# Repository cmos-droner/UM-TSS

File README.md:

# UM-TSS - CMOS Drumsynth
This is a circuit by Jacob Watters ([check the original block post](http://www.jacobwatters.com/blog/um-tss-drum-machine/)), I just did the PCB-layout. In agreement with Jacob this is released here as open hardware. Hopefully you enjoy the project and maybe you can even improve it!

## The circuit
The circuit is based around a couple of 40106 hex-schmitt triggers. I removed the divider from Jacobs layout to make every sound triggerable by itself. The trigger ins are protected by clamping diodes.

## PCB v1
PCB v1 has a couple of bugs (mainly because I used the wrong revision of Jacobs circuit **duh**). But the PCB can certainly be used to build a running circuit. Check the build guide for PCB rev. 1 [here](https://github.com/tommueller/UM-TSS/blob/master/schematics%20v1/BUILD.md) and the [BOM](https://github.com/tommueller/UM-TSS/blob/master/schematics%20v1/BOM.ods?raw=true)

## PCB v2
I already fixed most of the issued in the schematics for version 2. I hope that together we can make a second version of the PCB that runs more smooth!

## Case
I created a case which can be fabbed by a lasercutter. The SVG is available in the repo. The plans are for 3mm material! Here is an image of the first finished prototype (3mm colored HDF):

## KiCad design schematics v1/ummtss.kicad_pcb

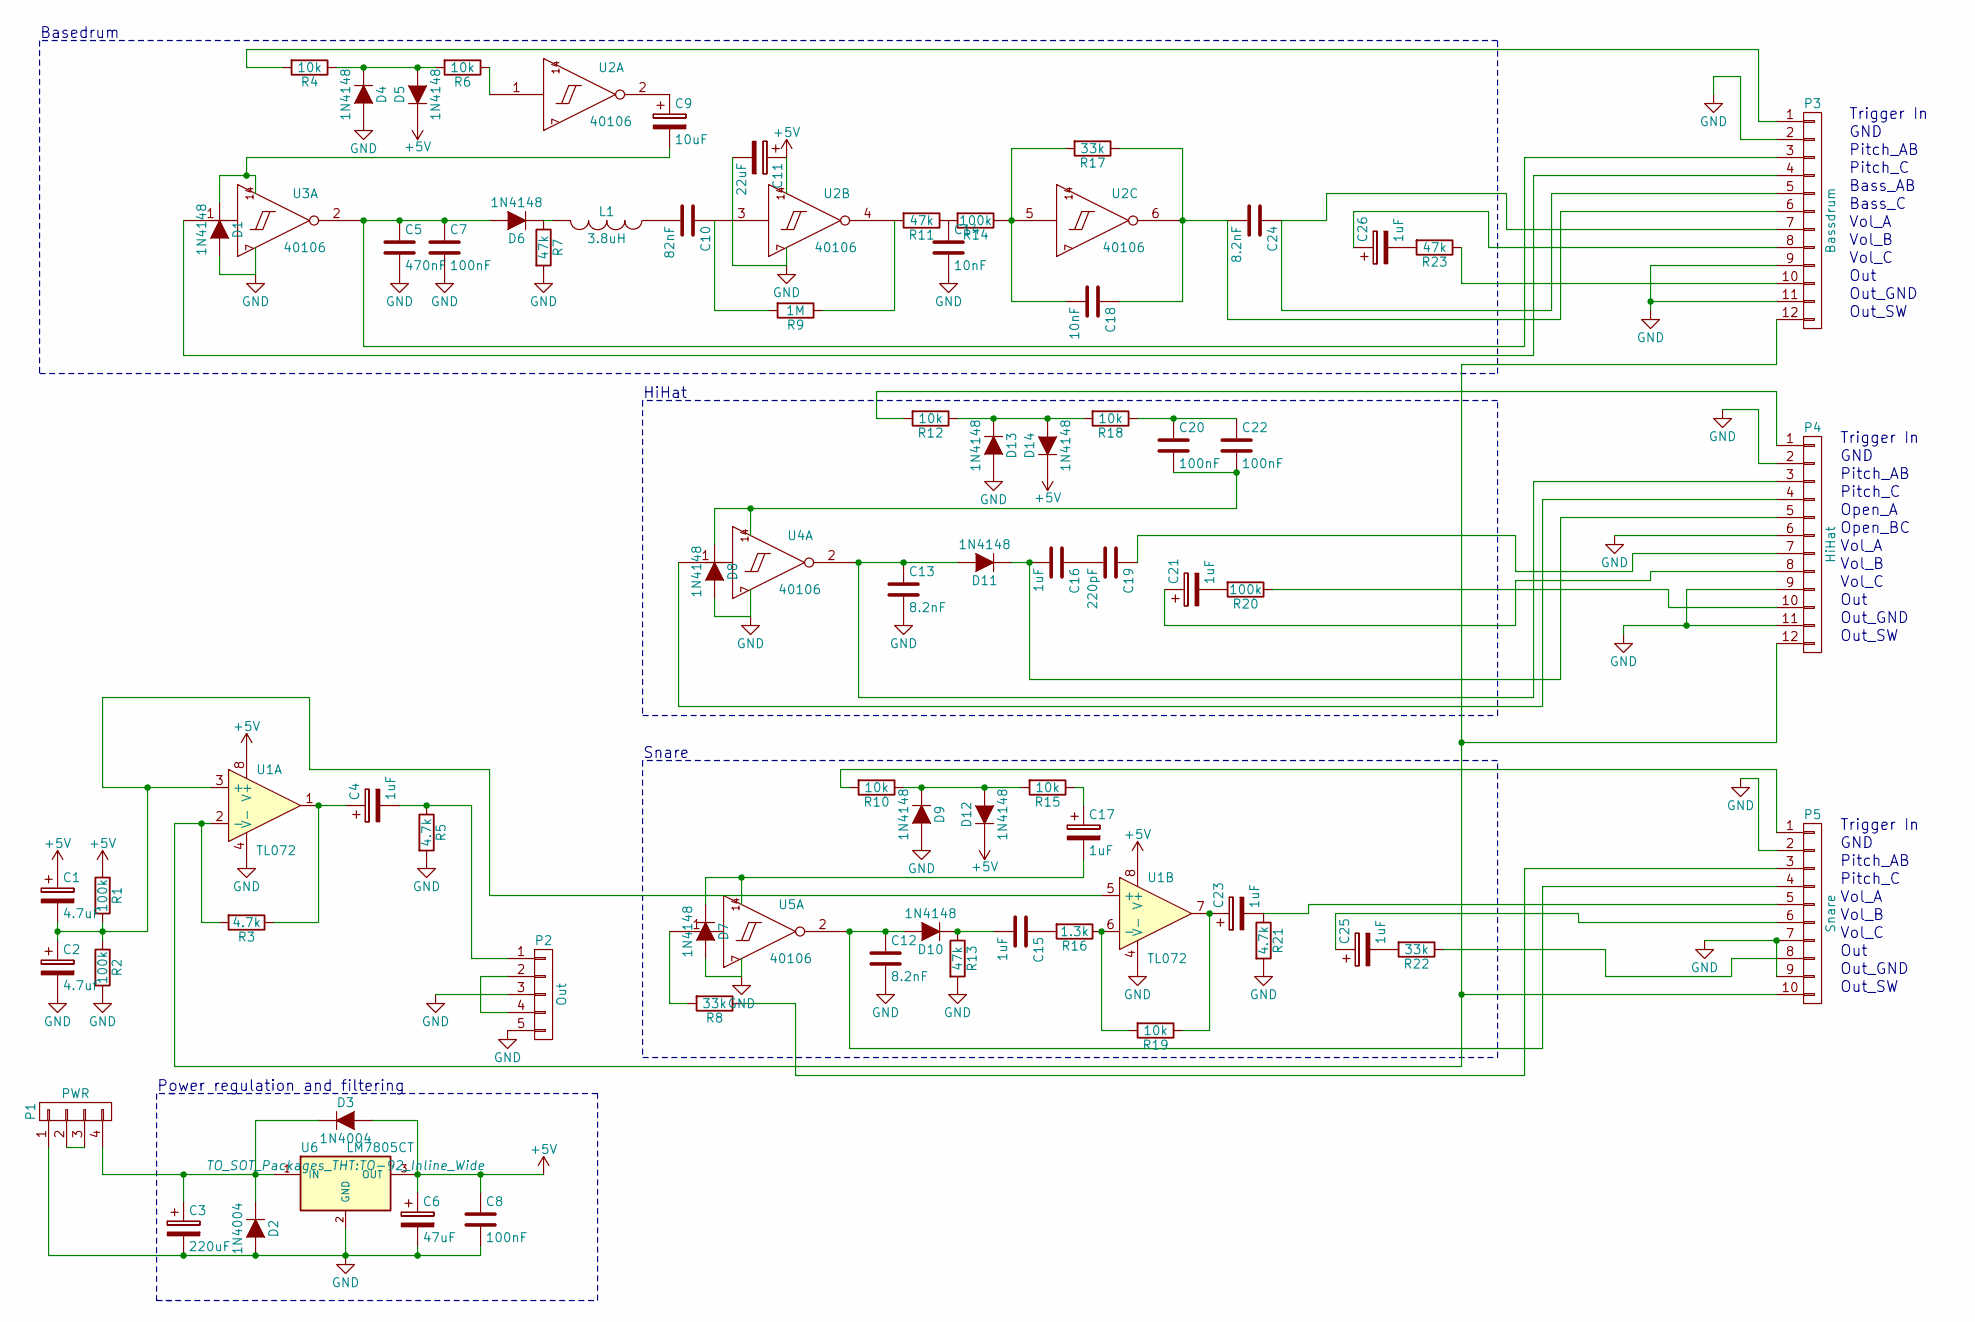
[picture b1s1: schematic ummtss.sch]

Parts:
C1: 4.7uF; C_Radial_D5_L11_P2.5
C2: 4.7uf; C_Radial_D5_L11_P2.5
C3: 220uF; C_Radial_D8_L11.5_P3.5
C4, C15, C16, C17, C21, C23, C25, C26: 1uF; C_Radial_D5_L11_P2.5
C5: 470nF; C_Rect_L4.5_W2.5_P3
C6: 47uF; C_Radial_D6.3_L11.2_P2.5
C7, C8, C20, C22: 100nF; C_Rect_L4.5_W2.5_P3
C9: 10uF; C_Radial_D5_L11_P2.5
C10: 82nF; C_Rect_L4.5_W2.5_P3
C11: 22uF; C_Radial_D5_L11_P2
C12, C13, C24: 8.2nF; C_Rect_L4.5_W2.5_P3
C14, C18: 10nF; C_Rect_L4.5_W2.5_P3
C19: 220pF; C_Rect_L4.5_W2.5_P3
D1, D4, D5, D6, D7, D8, D9, D10, D11, D12, D13, D14: 1N4148; Diode_DO-35_SOD27_Horizontal_RM10
D2, D3: 1N4004; Diode_DO-41_SOD81_Horizontal_RM10
L1: 3.8uH; Resistor_Horizontal_RM7mm_Wide
P1: PWR; Pin_Header_Straight_1x04
P2: Out; Pin_Header_Straight_1x05
P3: Bassdrum; Pin_Header_Straight_1x12
P4: HiHat; Pin_Header_Straight_1x12
P5: Snare; Pin_Header_Straight_1x10
R1, R2, R14, R20: 100k; Resistor_Horizontal_RM7mm_Wide
R3, R5, R21: 4.7k; Resistor_Horizontal_RM7mm_Wide
R4, R6, R10, R12, R15, R18, R19: 10k; Resistor_Horizontal_RM7mm_Wide
R7, R11, R13, R23: 47k; Resistor_Horizontal_RM7mm_Wide
R8, R17, R22: 33k; Resistor_Horizontal_RM7mm_Wide
R9: 1M; Resistor_Horizontal_RM7mm_Wide
R16: 1.3k; Resistor_Horizontal_RM7mm_Wide
U1: TL072; DIP-8_W7.62mm_LongPads
U2, U3, U4, U5: 40106; DIP-14_W7.62mm_LongPads
U6: LM7805CT; TO-92_Inline_Wide

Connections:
+5V: C1.1, C6.1, C8.1, C11.1, D3.2 (A), D5.1 (K), D12.1 (K), D14.1 (K), R1.1, U1.8 (V+), U2.14 (VDD_IN), U6.3 (OUT)
GND: C2.2, C3.2, C5.2, C6.2, C7.2, C8.2, C11.2, C12.2, C13.2, C14.2, D1.2 (A), D2.2 (A), D4.2 (A), D7.2 (A), D8.2 (A), D9.2 (A), D13.2 (A), P1.1, P2.3, P2.5, P3.2, P3.9, P3.11, P4.2, P4.6, P4.9, P4.11, P5.2, P5.7, P5.9, R2.2, R5.2, R7.2, R13.2, R21.2, U1.4 (V-), U2.7 (VSS_IN), U3.7 (VSS_IN), U4.7 (VSS_IN), U5.7 (VSS_IN), U6.2 (GND); also elsewhere on the board
unnamed: C1.2, C2.1, R1.2, R2.1, U1.3 (+), U1.5 (+)
unnamed 3: C3.1, D2.1 (K), D3.1 (K), P1.4, U6.1 (IN); also elsewhere on the board
unnamed: C4.1, R3.1, U1.1
unnamed 5: C4.2, P2.1, R5.1; also elsewhere on the board
unnamed 6: C5.1, C7.1, D6.2 (A), P3.3, U3.2 (Out); also elsewhere on the board
unnamed: C9.1, U2.2 (Out)
unnamed: C9.2, D1.1 (K), U3.14 (VDD_IN)
unnamed: C10.1, R9.2, U2.3 (In)
unnamed: C10.2, L1.1
unnamed 11: C12.1, D10.2 (A), P5.4, U5.2 (Out); also elsewhere on the board
unnamed 12: C13.1, D11.2 (A), P4.3, U4.2 (Out); also elsewhere on the board
unnamed: C14.1, R11.1, R14.2
unnamed: C15.1, R16.2
unnamed: C15.2, D10.1 (K), R13.1
unnamed: C16.1, C19.2
unnamed 17: C16.2, D11.1 (K), P4.5; also elsewhere on the board
unnamed: C17.1, R15.1
unnamed: C17.2, D7.1 (K), U5.14 (VDD_IN)
unnamed 20: C18.1, C24.2, P3.6, R17.1, U2.6 (Out); also elsewhere on the board
unnamed: C18.2, R17.2
unnamed 22: C19.1, P4.7; also elsewhere on the board
unnamed: C20.1, C22.1, R18.1
unnamed: C20.2, C22.2, D8.1 (K), U4.14 (VDD_IN)
unnamed 25: C21.1, P4.8; also elsewhere on the board
unnamed: C21.2, R20.2
unnamed: C23.1, R19.1, U1.7
unnamed 28: C23.2, P5.5, R21.1; also elsewhere on the board
unnamed 29: C24.1, P3.5, P3.7; also elsewhere on the board
unnamed 30: C25.1, P5.6; also elsewhere on the board
unnamed: C25.2, R22.2
unnamed 32: C26.1, P3.8; also elsewhere on the board
unnamed: C26.2, R23.2
unnamed: D4.1 (K), D5.2 (A), R4.1, R6.2
unnamed: D6.1 (K), L1.2, R7.1
unnamed: D9.1 (K), D12.2 (A), R10.1, R15.2
unnamed: D13.1 (K), D14.2 (A), R12.1, R18.2
unnamed 38: P1.2, P1.3; also elsewhere on the board
unnamed 39: P2.2, P2.4; also elsewhere on the board
unnamed 40: P3.1, R4.2; also elsewhere on the board
unnamed 41: P3.4, U3.1 (In); also elsewhere on the board
unnamed 42: P3.10, R23.1; also elsewhere on the board
unnamed 43: P3.12, P4.12, P5.10, R3.2, U1.2 (-); also elsewhere on the board
unnamed 44: P4.1, R12.2; also elsewhere on the board
unnamed 45: P4.4, U4.1 (In); also elsewhere on the board
unnamed 46: P4.10, R20.1; also elsewhere on the board
unnamed 47: P5.1, R10.2; also elsewhere on the board
unnamed 48: P5.3, R8.1; also elsewhere on the board
unnamed 49: P5.8, R22.1; also elsewhere on the board
unnamed: R6.1, U2.1 (In)
unnamed: R8.2, U5.1 (In)
unnamed: R9.1, R11.2, U2.4 (Out)
unnamed: R14.1, U2.5 (In)
unnamed: R16.1, R19.2, U1.6 (-)

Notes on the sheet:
Basedrum
HiHat
Snare
Power regulation and filtering
Trigger In
GND
Pitch_AB
Pitch_C
Bass_AB
Bass_C
Vol_A
Vol_B
Vol_C
Out
Out_GND
Out_SW
Open_A
Open_BC

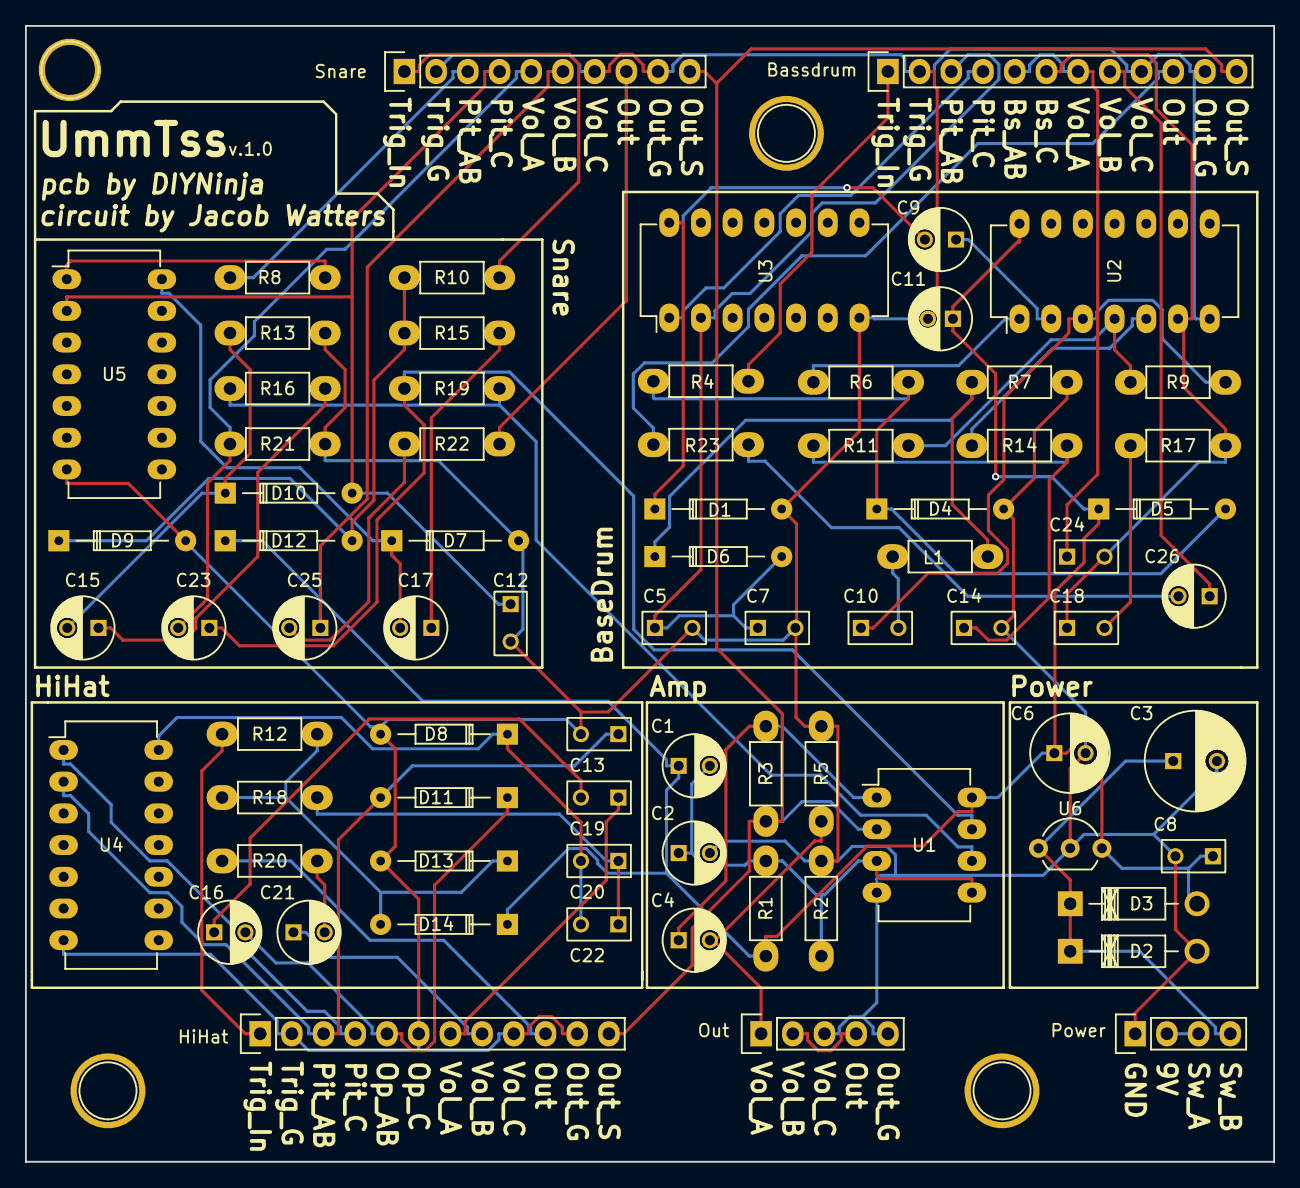
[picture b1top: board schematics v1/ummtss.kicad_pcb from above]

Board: 2 copper layers, 100.0 x 91.0 mm, 79 parts (0 on the bottom side), 55 nets.

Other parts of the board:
Bassdrum: Bassdrum; Pin_Header_Straight_1x12
H1, H2, H3, H4: 1pin
HiHat: HiHat; Pin_Header_Straight_1x12
Out: Out; Pin_Header_Straight_1x05
Power: PWR; Pin_Header_Straight_1x04
Snare: Snare; Pin_Header_Straight_1x10

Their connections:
GND: Bassdrum.2, Bassdrum.9, Bassdrum.11, HiHat.2, HiHat.6, HiHat.9, HiHat.11, Out.3, Out.5, Power.1, Snare.2, Snare.7, Snare.9; also elsewhere on the board
unnamed 3: Power.4; also elsewhere on the board
unnamed 5: Out.1; also elsewhere on the board
unnamed 6: Bassdrum.3; also elsewhere on the board
unnamed 11: Snare.4; also elsewhere on the board
unnamed 12: HiHat.3; also elsewhere on the board
unnamed 17: HiHat.5; also elsewhere on the board
unnamed 20: Bassdrum.6; also elsewhere on the board
unnamed 22: HiHat.7; also elsewhere on the board
unnamed 25: HiHat.8; also elsewhere on the board
unnamed 28: Snare.5; also elsewhere on the board
unnamed 29: Bassdrum.5, Bassdrum.7; also elsewhere on the board
unnamed 30: Snare.6; also elsewhere on the board
unnamed 32: Bassdrum.8; also elsewhere on the board
unnamed 38: Power.2, Power.3; also elsewhere on the board
unnamed 39: Out.2, Out.4; also elsewhere on the board
unnamed 40: Bassdrum.1; also elsewhere on the board
unnamed 41: Bassdrum.4; also elsewhere on the board
unnamed 42: Bassdrum.10; also elsewhere on the board
unnamed 43: Bassdrum.12, HiHat.12, Snare.10; also elsewhere on the board
unnamed 44: HiHat.1; also elsewhere on the board
unnamed 45: HiHat.4; also elsewhere on the board
unnamed 46: HiHat.10; also elsewhere on the board
unnamed 47: Snare.1; also elsewhere on the board
unnamed 48: Snare.3; also elsewhere on the board
unnamed 49: Snare.8; also elsewhere on the board

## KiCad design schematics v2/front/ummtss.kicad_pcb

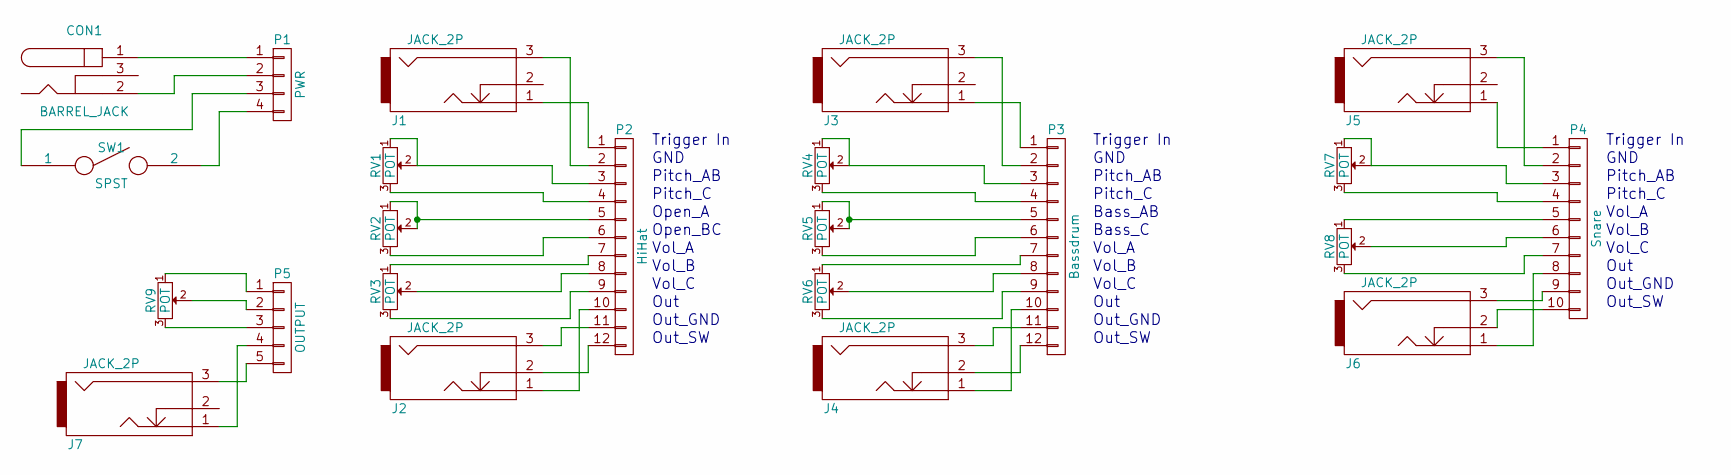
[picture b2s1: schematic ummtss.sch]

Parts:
CON1: BARREL_JACK
J1, J2, J3, J4, J5, J6, J7: JACK_2P; jack-PJ301M
P1: PWR; Pin_Header_Straight_1x04
P2: HiHat; Pin_Header_Straight_1x12
P3: Bassdrum; Pin_Header_Straight_1x12
P4: Snare; Pin_Header_Straight_1x10
P5: OUTPUT; Pin_Header_Straight_1x05
RV1, RV2, RV3, RV4, RV5, RV6, RV7, RV8, RV9: POT; pot_alpha-9mm--vertical
SW1: SPST; SW_Micro_SPST

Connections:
unnamed: CON1.1, P1.1
unnamed: CON1.2, P1.2
unnamed: J1.1, P2.1
unnamed: J1.3, P2.2
unnamed: J2.1, P2.10
unnamed: J2.2, P2.12
unnamed: J2.3, P2.11
unnamed: J3.1, P3.1
unnamed: J3.3, P3.2
unnamed: J4.1, P3.10
unnamed: J4.2, P3.12
unnamed: J4.3, P3.11
unnamed: J5.1, P4.1
unnamed: J5.3, P4.2
unnamed: J6.1, P4.8
unnamed: J6.2, P4.10
unnamed: J6.3, P4.9
unnamed: J7.1, P5.4
unnamed: J7.3, P5.5
unnamed: P1.3, SW1.1
unnamed: P1.4, SW1.2
unnamed: P2.3, RV1.1, RV1.2
unnamed: P2.4, RV1.3
unnamed: P2.5, RV2.1, RV2.2
unnamed: P2.6, RV2.3
unnamed: P2.7, RV3.1
unnamed: P2.8, RV3.2
unnamed: P2.9, RV3.3
unnamed: P3.3, RV4.1, RV4.2
unnamed: P3.4, RV4.3
unnamed: P3.5, RV5.1, RV5.2
unnamed: P3.6, RV5.3
unnamed: P3.7, RV6.1
unnamed: P3.8, RV6.2
unnamed: P3.9, RV6.3
unnamed: P4.3, RV7.1, RV7.2
unnamed: P4.4, RV7.3
unnamed: P4.5, RV8.1
unnamed: P4.6, RV8.2
unnamed: P4.7, RV8.3
unnamed: P5.1, RV9.1
unnamed: P5.2, RV9.2
unnamed: P5.3, RV9.3

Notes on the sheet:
Trigger In
GND
Pitch_AB
Pitch_C
Bass_AB
Bass_C
Vol_A
Vol_B
Vol_C
Out
Out_GND
Out_SW
Open_A
Open_BC

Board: 2 copper layers, 23 parts (0 on the bottom side), 43 nets, no tracks yet.

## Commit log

2017-01-09 Add project files
2017-01-09 upload sound demo
2017-01-09 rename case folder
2017-01-09 add images
2017-01-09 flip image
2017-01-09 remove old note from case
2017-01-09 Add buildguide
2017-01-09 add image to readme
2017-01-09 add material desc
2017-01-09 add bom
2017-01-09 add bom to readme
2017-01-09 add build hints
2017-01-09 mention wrong pots lebales
2017-01-12 fix twoo small holes in case
2017-01-12 update build guide
2017-01-12 add hint for instrument outs
2017-01-12 add dc jack info
2017-01-20 add eps of case
